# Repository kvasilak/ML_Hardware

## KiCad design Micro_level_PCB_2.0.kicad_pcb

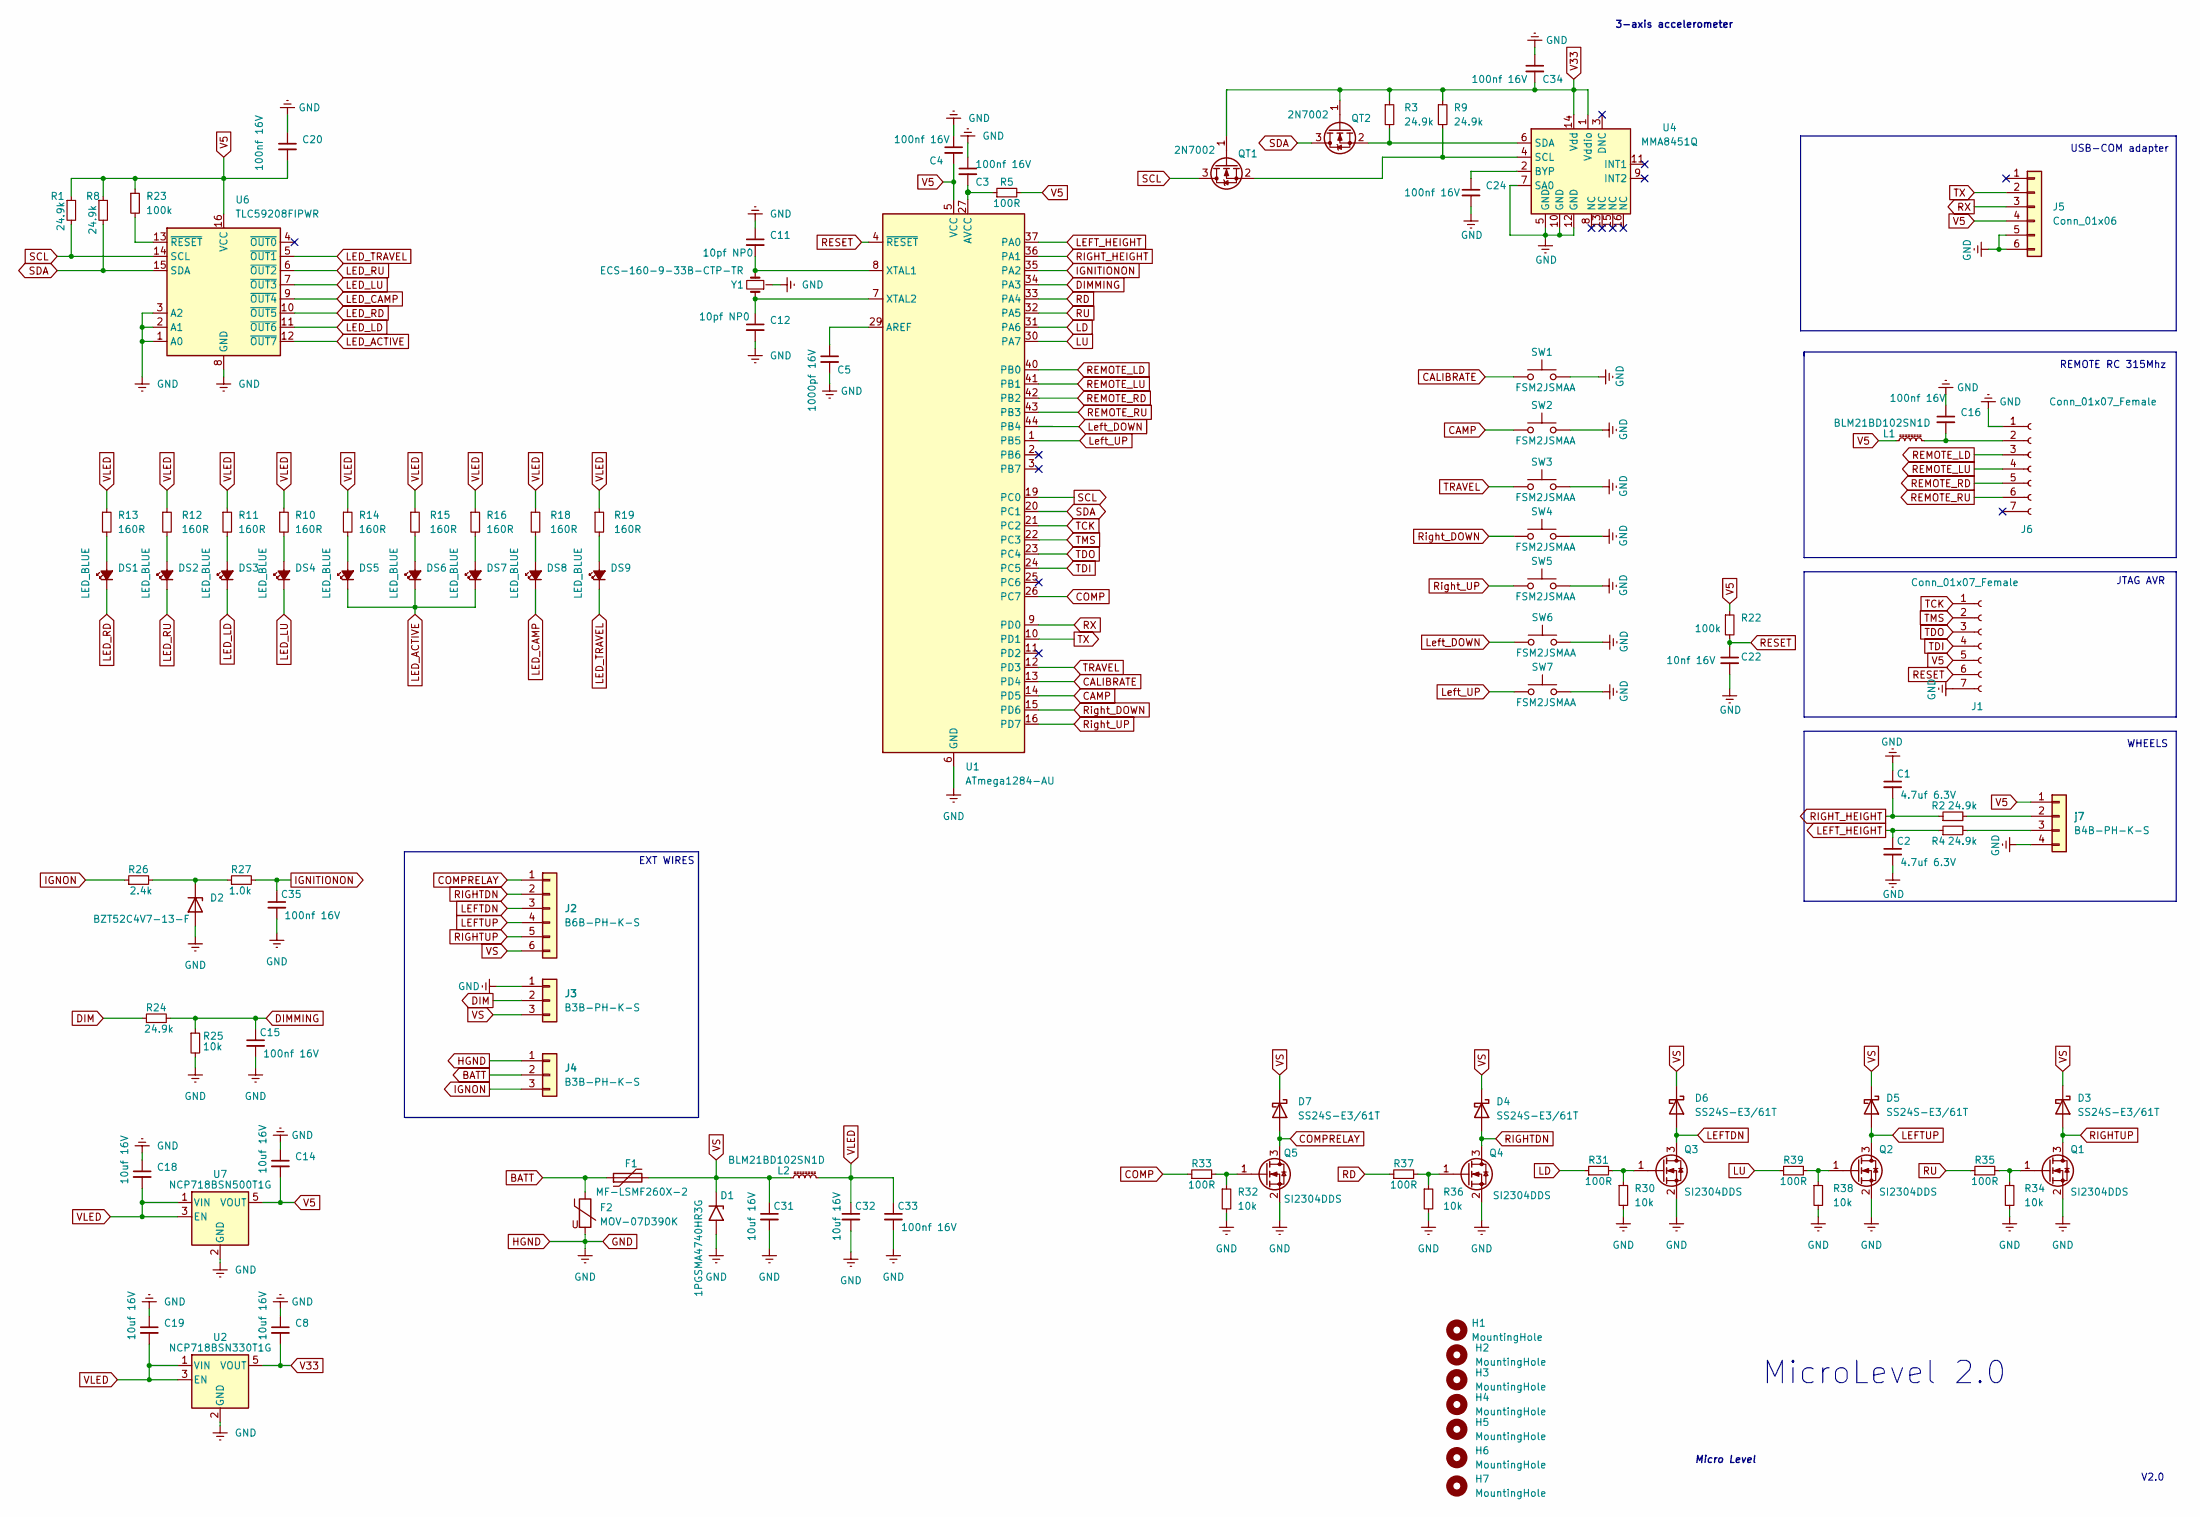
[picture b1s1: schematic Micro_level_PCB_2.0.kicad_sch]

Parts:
C1, C2: 4.7uf 6.3V; C_0805_2012Metric
C3, C4, C15, C16, C20, C24, C33, C34, C35: 100nf 16V; C_0805_2012Metric
C5: 1000pf 16V; C_0805_2012Metric
C8, C14, C18, C19, C31, C32: 10uf 16V; C_0805_2012Metric
C11, C12: 10pf NP0; C_0805_2012Metric
C22: 10nf 16V; C_0805_2012Metric
D1: 1PGSMA4740HR3G; D_SMA
D2: BZT52C4V7-13-F; D_SOD-123
D3, D4, D5, D6, D7: SS24S-E3/61T; D_SMA
DS1, DS2, DS3, DS4, DS5, DS6, DS7, DS8, DS9: LED_BLUE; LED_PLCC-2
F1: MF-LSMF260X-2; Fuse_2920_7451Metric
F2: MOV-07D390K; RV_Disc_D7mm_W3.4mm_P5mm
H1, H2, H3, H4, H5, H6, H7: MountingHole; MountingHole_3.2mm_M3_Pad_TopBottom
J1, J6: Conn_01x07_Female; PinHeader_1x07_P2.54mm_Vertical
J2: B6B-PH-K-S; JST_PH_B6B-PH-K_1x06_P2.00mm_Vertical
J3, J4: B3B-PH-K-S; JST_PH_B3B-PH-K_1x03_P2.00mm_Vertical
J5: Conn_01x06; PinHeader_1x06_P2.54mm_Vertical
L1, L2: BLM21BD102SN1D; L_0805_2012Metric
Q1, Q2, Q3, Q4, Q5: SI2304DDS; SOT-23
QT1, QT2: 2N7002; SOT-23
R1, R2, R3, R4, R8, R9, R24: 24.9k; R_0805_2012Metric
R5, R31, R33, R35, R37, R39: 100R; R_0805_2012Metric
R10, R11, R12, R13, R14, R15, R16, R18, R19: 160R; R_1206_3216Metric
R22, R23: 100k; R_0805_2012Metric
R25, R30, R32, R34, R36, R38: 10k; R_0805_2012Metric
R26: 2.4k; R_0805_2012Metric
R27: 1.0k; R_0805_2012Metric
SW1, SW2, SW3, SW4, SW5, SW6, SW7: FSM2JSMAA; SW_Push_1P1T_NO_6x6mm_H5.0mm
U1: ATmega1284-AU; TQFP-44_10x10mm_P0.8mm
U2: NCP718BSN330T1G; SOT-23-5
U4: MMA8451Q; QFN16_FRE
U6: TLC59208FIPWR; TSSOP-16_4.4x5mm_P0.65mm
U7: NCP718BSN500T1G; SOT-23-5
Y1: ECS-160-9-33B-CTP-TR; Crystal_SMD_3225-4Pin_3.2x2.5mm
j7: B4B-PH-K-S; JST_PH_B4B-PH-K_1x04_P2.00mm_Vertical

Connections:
BATT: F1.1, F2.1, J4.2
CALIBRATE: SW1.1 (A), SW1.2 (A), U1.13 (PD4)
CAMP: SW2.1 (A), SW2.2 (A), U1.14 (PD5)
COMP: R33.1, U1.26 (PC7)
COMPRELAY: D7.2 (A), J2.1, Q5.3 (D)
DIM: J3.2, R24.1
DIMMING: C15.1, R24.2, R25.1, U1.34 (PA3)
GND: C1.1, C2.2, C3.1, C4.1, C5.2, C8.1, C11.1, C12.2, C14.1, C15.2, C16.1, C18.1, C19.1, C20.1, C22.2, C24.2, C31.2, C32.2, C33.2, C34.1, C35.2, D1.2 (A2), D2.2 (A), F2.2, J1.7, J3.1, J4.1, J5.5, J5.6, J6.1, Q1.2 (S), Q2.2 (S), Q3.2 (S), Q4.2 (S), Q5.2 (S), R25.2, R30.2, R32.2, R34.2, R36.2, R38.2, SW1.3 (B), SW1.4 (B), SW2.3 (B), SW2.4 (B), SW3.3 (B), SW3.4 (B), SW4.3 (B), SW4.4 (B), SW5.3 (B), SW5.4 (B), SW6.3 (B), SW6.4 (B), SW7.3 (B), SW7.4 (B), U1.6 (GND), U1.18 (GND), U1.28 (GND), U1.39 (GND), U2.2 (GND), U4.5 (GND), U4.7 (SA0), U4.10 (GND), U4.12 (GND), U6.1 (A0), U6.2 (A1), U6.3 (A2), U6.8 (GND), U7.2 (GND), Y1.2 (GND), Y1.4 (GND), j7.4
IGNITIONON: C35.1, R27.2, U1.35 (PA2)
IGNON: J4.3, R26.1
LD: R31.1, U1.31 (PA6)
LED_ACTIVE: DS5.1 (K), DS6.1 (K), DS7.1 (K), U6.12 (~OUT7)
LED_CAMP: DS8.1 (K), U6.9 (~OUT4)
LED_LD: DS3.1 (K), U6.11 (~OUT6)
LED_LU: DS4.1 (K), U6.7 (~OUT3)
LED_RD: DS1.1 (K), U6.10 (~OUT5)
LED_RU: DS2.1 (K), U6.6 (~OUT2)
LED_TRAVEL: DS9.1 (K), U6.5 (~OUT1)
LEFTDN: D6.2 (A), J2.3, Q3.3 (D)
LEFTUP: D5.2 (A), J2.4, Q2.3 (D)
LEFT_HEIGHT: C2.1, R4.1, U1.37 (PA0)
LU: R39.1, U1.30 (PA7)
Left_DOWN: SW6.1 (A), SW6.2 (A), U1.44 (PB4)
Left_UP: SW7.1 (A), SW7.2 (A), U1.1 (PB5)
unnamed: C3.2, R5.1, U1.27 (AVCC)
unnamed: C5.1, U1.29 (AREF)
unnamed: C11.2, U1.8 (XTAL1), Y1.3
unnamed: C12.1, U1.7 (XTAL2), Y1.1
unnamed: C16.2, J6.2, L1.2
unnamed: C24.1, U4.2 (BYP)
unnamed: D2.1 (K), R26.2, R27.1
unnamed: DS1.2 (A), R13.2
unnamed: DS2.2 (A), R12.2
unnamed: DS3.2 (A), R11.2
unnamed: DS4.2 (A), R10.2
unnamed: DS5.2 (A), R14.2
unnamed: DS6.2 (A), R15.2
unnamed: DS7.2 (A), R16.2
unnamed: DS8.2 (A), R18.2
unnamed: DS9.2 (A), R19.2
unnamed: Q1.1 (G), R34.1, R35.2
unnamed: Q2.1 (G), R38.1, R39.2
unnamed: Q3.1 (G), R30.1, R31.2
unnamed: Q4.1 (G), R36.1, R37.2
unnamed: Q5.1 (G), R32.1, R33.2
unnamed: QT1.2 (S), R9.2, U4.4 (SCL)
unnamed: QT2.2 (S), R3.2, U4.6 (SDA)
unnamed: R2.2, j7.2
unnamed: R4.2, j7.3
unnamed: R23.2, U6.13 (~RESET)
RD: R37.1, U1.33 (PA4)
REMOTE_LD: J6.3, U1.40 (PB0)
REMOTE_LU: J6.4, U1.41 (PB1)
REMOTE_RD: J6.5, U1.42 (PB2)
REMOTE_RU: J6.6, U1.43 (PB3)
RESET: C22.1, J1.6, R22.2, U1.4 (~RESET)
RIGHTDN: D4.2 (A), J2.2, Q4.3 (D)
RIGHTUP: D3.2 (A), J2.5, Q1.3 (D)
RIGHT_HEIGHT: C1.2, R2.1, U1.36 (PA1)
RU: R35.1, U1.32 (PA5)
RX: J5.3, U1.9 (PD0)
Right_DOWN: SW4.1 (A), SW4.2 (A), U1.15 (PD6)
Right_UP: SW5.1 (A), SW5.2 (A), U1.16 (PD7)
SCL: QT1.3 (D), R1.2, U1.19 (PC0), U6.14 (SCL)
SDA: QT2.3 (D), R8.2, U1.20 (PC1), U6.15 (SDA)
TCK: J1.1, U1.21 (PC2)
TDI: J1.4, U1.24 (PC5)
TDO: J1.3, U1.23 (PC4)
TMS: J1.2, U1.22 (PC3)
TRAVEL: SW3.1 (A), SW3.2 (A), U1.12 (PD3)
TX: J5.2, U1.10 (PD1)
V5: C4.2, C14.2, C20.2, J1.5, J5.4, L1.1, R1.1, R5.2, R8.1, R22.1, R23.1, U1.5 (VCC), U1.17 (VCC), U1.38 (VCC), U6.16 (VCC), U7.5 (VOUT), j7.1
V33: C8.2, C34.2, QT1.1 (G), QT2.1 (G), R3.1, R9.1, U2.5 (VOUT), U4.1 (Vddio), U4.14 (Vdd)
VLED: C18.2, C19.2, C32.1, C33.1, L2.2, R10.1, R11.1, R12.1, R13.1, R14.1, R15.1, R16.1, R18.1, R19.1, U2.1 (VIN), U2.3 (EN), U7.1 (VIN), U7.3 (EN)
VS: C31.1, D1.1 (A1), D3.1 (K), D4.1 (K), D5.1 (K), D6.1 (K), D7.1 (K), F1.2, J2.6, J3.3, L2.1

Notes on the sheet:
REMOTE RC 315Mhz
USB-COM adapter
WHEELS
3-axis accelerometer
V2.0
Micro Level
EXT WIRES
MicroLevel 2.0
JTAG AVR

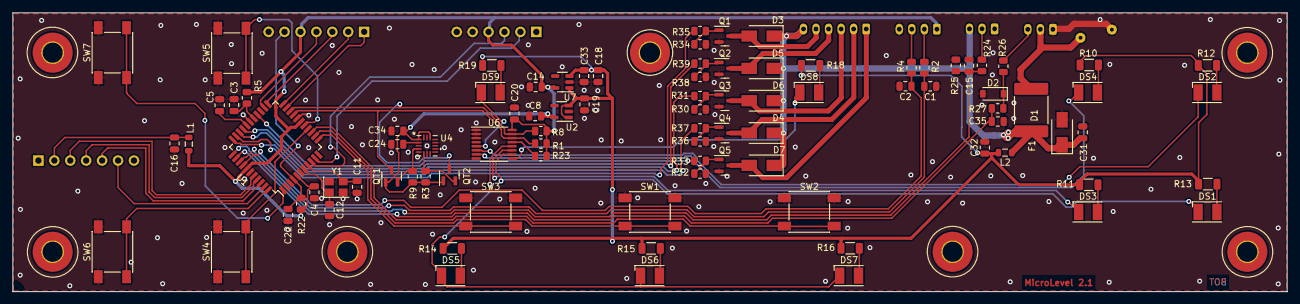
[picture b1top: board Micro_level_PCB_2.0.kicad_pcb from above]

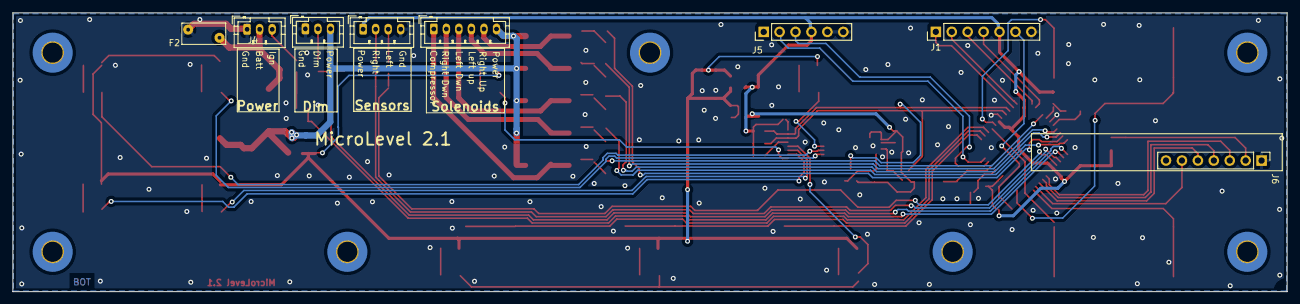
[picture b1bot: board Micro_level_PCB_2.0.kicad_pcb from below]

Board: 2 copper layers, 203.2 x 44.5 mm, 107 parts (8 on the bottom side), 75 nets.

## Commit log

2023-02-06 4 button up/down
2023-02-19 move buttons, change jtag connector
2023-02-19 move resistor
2023-02-19 fix compressor text
2023-02-27 4 up/down buttons, remove 2x5 jtag
